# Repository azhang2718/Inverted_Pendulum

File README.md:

# Inverted Pendulum Control System

This page showcases an inverted pendulum on a cart, stabilized in real time by a custom PCB running a PID controller on a TI MSPM0G3507 as part of our final project for **ELEC 327 — Junior Design Lab**.

**Team:** Anthony Zhang · Bilin Yang · Brandon Sung · Setsuna Jiang

---

## Overview

The inverted pendulum is a classic control-theory benchmark: a rigid rod pivots freely on top of a cart that slides along a linear rail, and the controller must drive the cart left and right fast enough to keep the rod balanced upright. The upright position is inherently unstable, so any small tilt has to be detected and corrected before gravity wins.

Our implementation reads the pendulum angle from an AS5600 magnetic encoder over I²C, runs a PID loop at 200 Hz on a custom PCB, and drives a NEMA 17 stepper through a DRV8825 to move the cart along a V-slot aluminum rail.

---

## Hardware

| Component | Part | Role |
|---|---|---|
| Microcontroller | TI MSPM0G3507 | Runs the 200 Hz PID loop |
| Angle sensor | AS5600 magnetic encoder (I²C) | Reads pendulum angle (12-bit) |
| Magnet | Diametrically magnetized, 6 mm OD | Required for AS5600 to detect rotation |
| Motor | NEMA 17 stepper | Drives the cart |
| Motor driver | DRV8825 | STEP/DIR interface, 1/8 microstepping |
| Rail | V-slot aluminum extrusion + GT2 belt | Cart travel |
| Cart | V-slot gantry plate + V-wheels | Rides the rail |
| Bearings | 625RS | Pulley + idler support |
| Endstops | Limit switches (×2) | Homing on startup |
| Power | 12 V / 5 A supply | Motor + logic rail |
| Regulator | LM1117 3.3 V LDO | Logic supply |
| Pendulum | 6 mm × 300 mm steel rod | The thing being balanced |

The full PCB design is in `pcb/` as a KiCad project. Open `*.kicad_pro` in the KiCad project manager to view the schematic and layout

---

## Software

### Control loop

A standard PID controller on the pendulum angle:

- **P** — proportional response to current tilt
- **I** — corrects for slow drift / sensor offset
- **D** — damps oscillation by reacting to angular velocity

The loop runs at 200 Hz. PID gains are stored as integers scaled by 100 so all arithmetic stays in fixed-point — no FPU needed, and the timing is deterministic.

### `config.h`

Every tunable value in the project lives in a single header. The idea is that PID tuning is iterative — you change a number, flash, test, repeat — and having every constant in one place makes that loop fast and error-free.

Things in `config.h`:
- `KP`, `KI`, `KD` — PID gains (scaled ×100)
- `MIN_STEP_RATE`, `MAX_STEP_RATE` — motor speed bounds (prevents stall and runaway)
- `DEADBAND` — angle window where no correction is applied
- `ENGAGE_THRESHOLD` — angle within which the controller activates
- `GIVE_UP_THRESHOLD` — angle past which the controller disengages
- `INTEGRAL_CLAMP` — anti-windup limit on the integral term
- `MOTOR_DIR_SIGN` — direction polarity

### I²C driver (AS5600)

The angle sensor is read over I²C from the raw-angle register. The driver:

1. Waits for the bus to be idle
2. Flushes the TX FIFO
3. Writes the target register address
4. Reads back two bytes → 12-bit angle

Every busy-wait loop has a **timeout counter** that decrements and returns an error code if it hits zero. Without these, a single bad I²C transaction could lock the entire control loop — and on a pendulum that's trying to balance, a hang means it falls instantly.

### Startup sequence

1. Init peripherals (I²C, timers, GPIO)
2. Home the cart against the limit switches and zero the step counter
3. Move cart to center of the rail
4. Wait until the pendulum is within `ENGAGE_THRESHOLD` of vertical
5. Enable PID loop

---

## Building & Flashing

1. Install **Code Composer Studio** (or use the TI Arm Clang toolchain directly).
2. Open the firmware project, build, and flash via the SWD header on the PCB.
3. Adjust values in `inc/config.h` as needed and reflash to tune.

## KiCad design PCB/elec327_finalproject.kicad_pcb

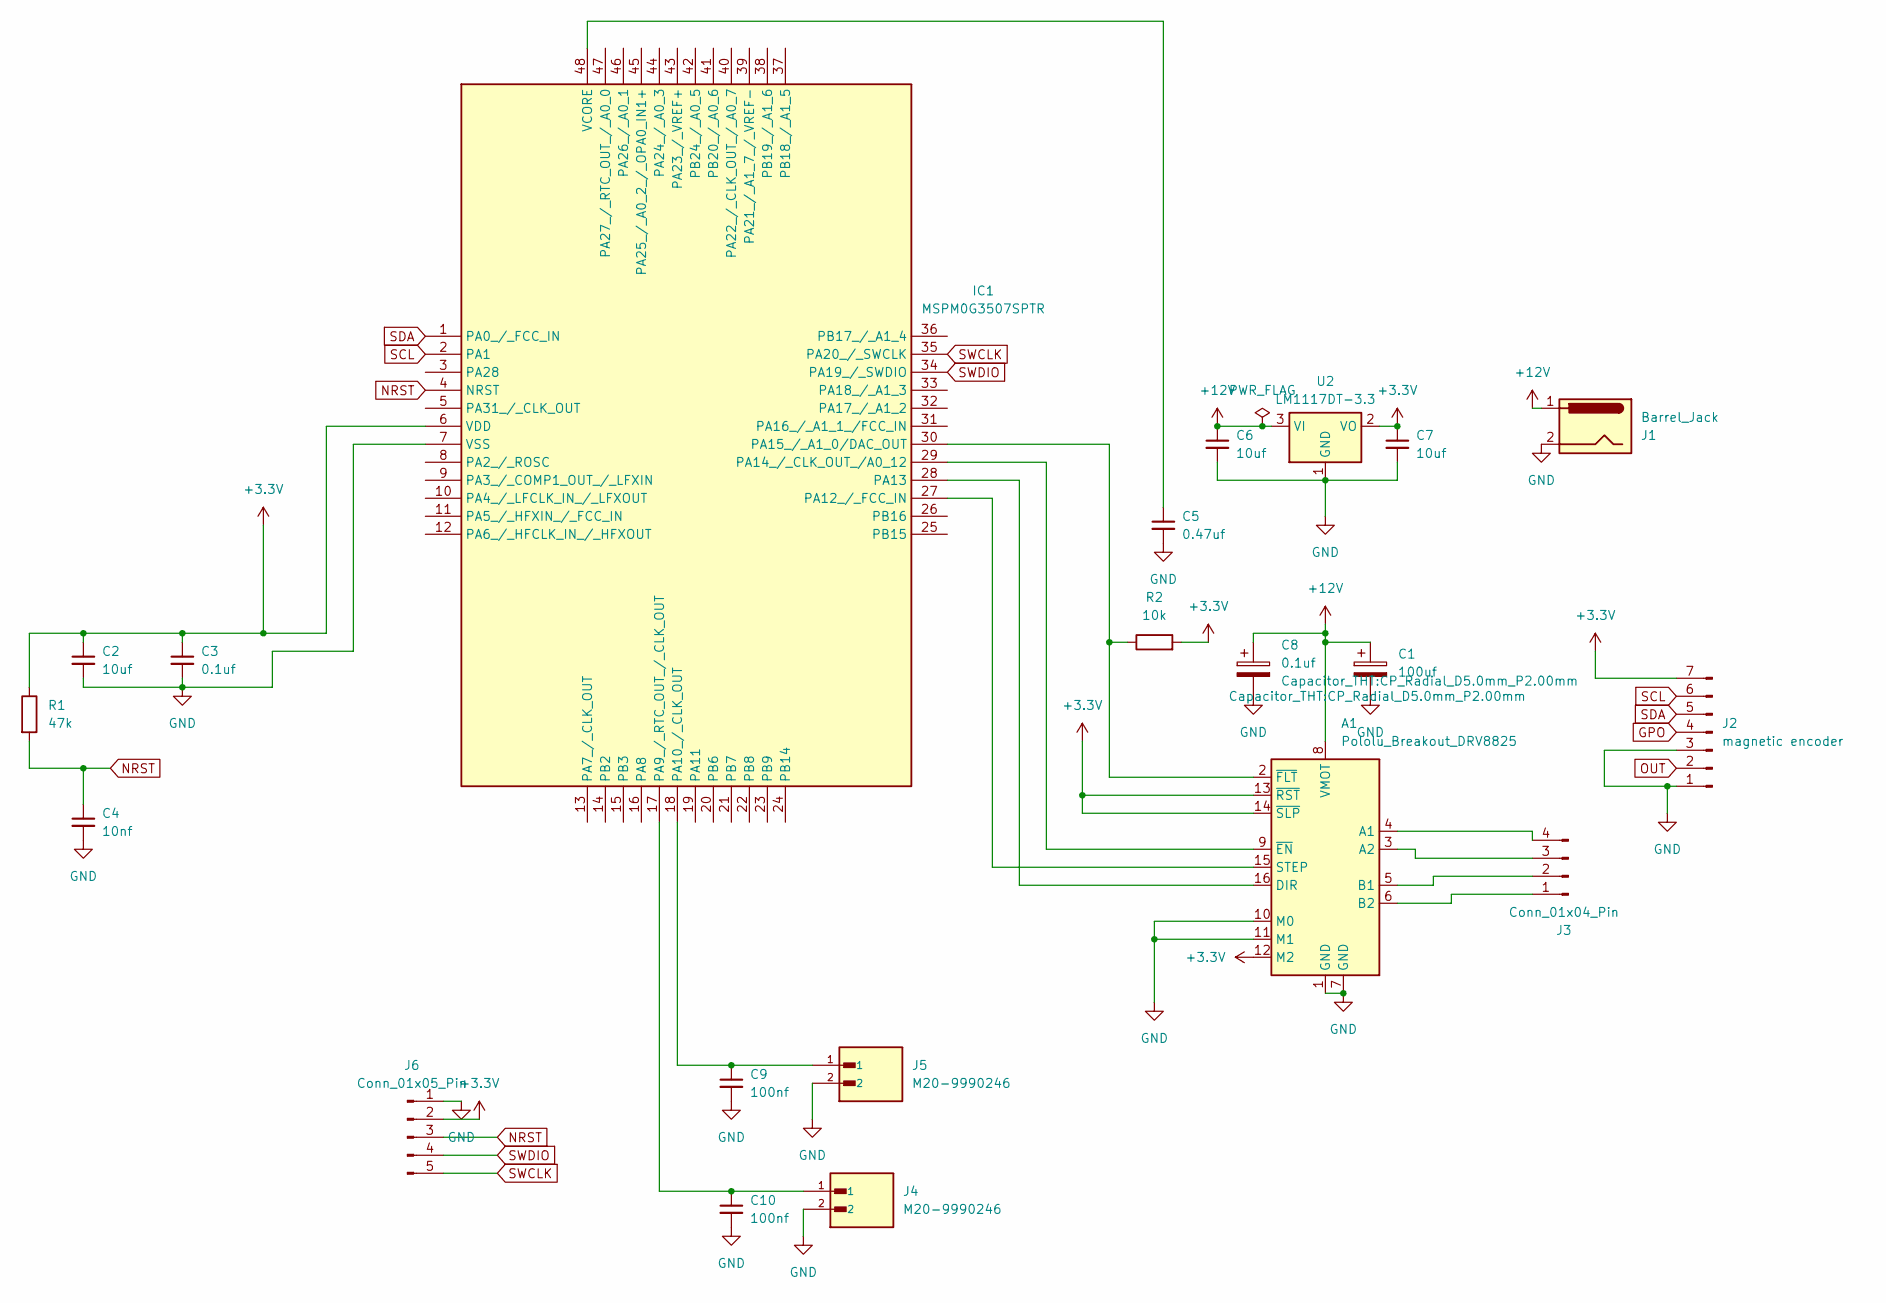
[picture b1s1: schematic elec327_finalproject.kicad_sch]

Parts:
A1: Pololu_Breakout_DRV8825; Pololu_Breakout-16_15.2x20.3mm
C1: 100uf; CP_Radial_D5.0mm_P2.00mm
C2, C6, C7: 10uf; C_0805_2012Metric_Pad1.18x1.45mm_HandSolder
C3: 0.1uf; C_0805_2012Metric_Pad1.18x1.45mm_HandSolder
C4: 10nf; C_0805_2012Metric_Pad1.18x1.45mm_HandSolder
C5: 0.47uf; C_0805_2012Metric_Pad1.18x1.45mm_HandSolder
C8: 0.1uf; CP_Radial_D5.0mm_P2.00mm
C9, C10: 100nf; C_0805_2012Metric_Pad1.18x1.45mm_HandSolder
IC1: MSPM0G3507SPTR; QFP50P900X900X160-48N; Mouser Part Number 595-MSPM0G3507SPTR
J1: Barrel_Jack; BarrelJack_SwitchcraftConxall_RAPC10U_Horizontal
J2: magnetic encoder; PinHeader_1x07_P2.54mm_Vertical
J3: Conn_01x04_Pin; PinHeader_1x04_P2.54mm_Vertical
J4, J5: M20-9990246; HARWIN_M20-9990246; PARTREV 14
J6: Conn_01x05_Pin; PinHeader_1x05_P2.54mm_Vertical
R1: 47k; R_0805_2012Metric_Pad1.20x1.40mm_HandSolder
R2: 10k; R_0805_2012Metric_Pad1.20x1.40mm_HandSolder
U2: LM1117DT-3.3; TO-252-3_TabPin2

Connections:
+3.3V: A1.12 (M2), A1.13 (~RST), A1.14 (~SLP), C2.1, C3.1, C7.1, IC1.6 (VDD), J2.7, J6.2, R1.1, R2.2, U2.2 (VO)
+12V: A1.8 (VMOT), C1.1, C6.1, C8.1, J1.1, U2.3 (VI)
GND: A1.1 (GND), A1.7 (GND), A1.10 (M0), A1.11 (M1), C1.2, C2.2, C3.2, C4.2, C5.2, C6.2, C7.2, C8.2, C9.2, C10.2, IC1.7 (VSS), J1.2, J2.1, J2.3, J4.2, J5.2, J6.1, U2.1 (GND)
GPO: J2.4
NRST: C4.1, IC1.4 (NRST), J6.3, R1.2
unnamed: A1.4 (A1), J3.4
unnamed: A1.3 (A2), J3.3
unnamed: A1.5 (B1), J3.2
unnamed: A1.6 (B2), J3.1
unnamed: A1.16 (DIR), IC1.28 (PA13)
unnamed: A1.15 (STEP), IC1.27 (PA12_/_FCC_IN)
unnamed: A1.9 (~EN), IC1.29 (PA14_/_CLK_OUT_/A0_12)
unnamed: A1.2 (~FLT), IC1.30 (PA15_/_A1_0/DAC_OUT), R2.1
unnamed: C10.1, IC1.17 (PA9_/_RTC_OUT_/_CLK_OUT), J4.1
unnamed: C9.1, IC1.18 (PA10_/_CLK_OUT), J5.1
unnamed: C5.1, IC1.48 (VCORE)
OUT: J2.2
SCL: IC1.2 (PA1), J2.6
SDA: IC1.1 (PA0_/_FCC_IN), J2.5
SWCLK: IC1.35 (PA20_/_SWCLK), J6.5
SWDIO: IC1.34 (PA19_/_SWDIO), J6.4

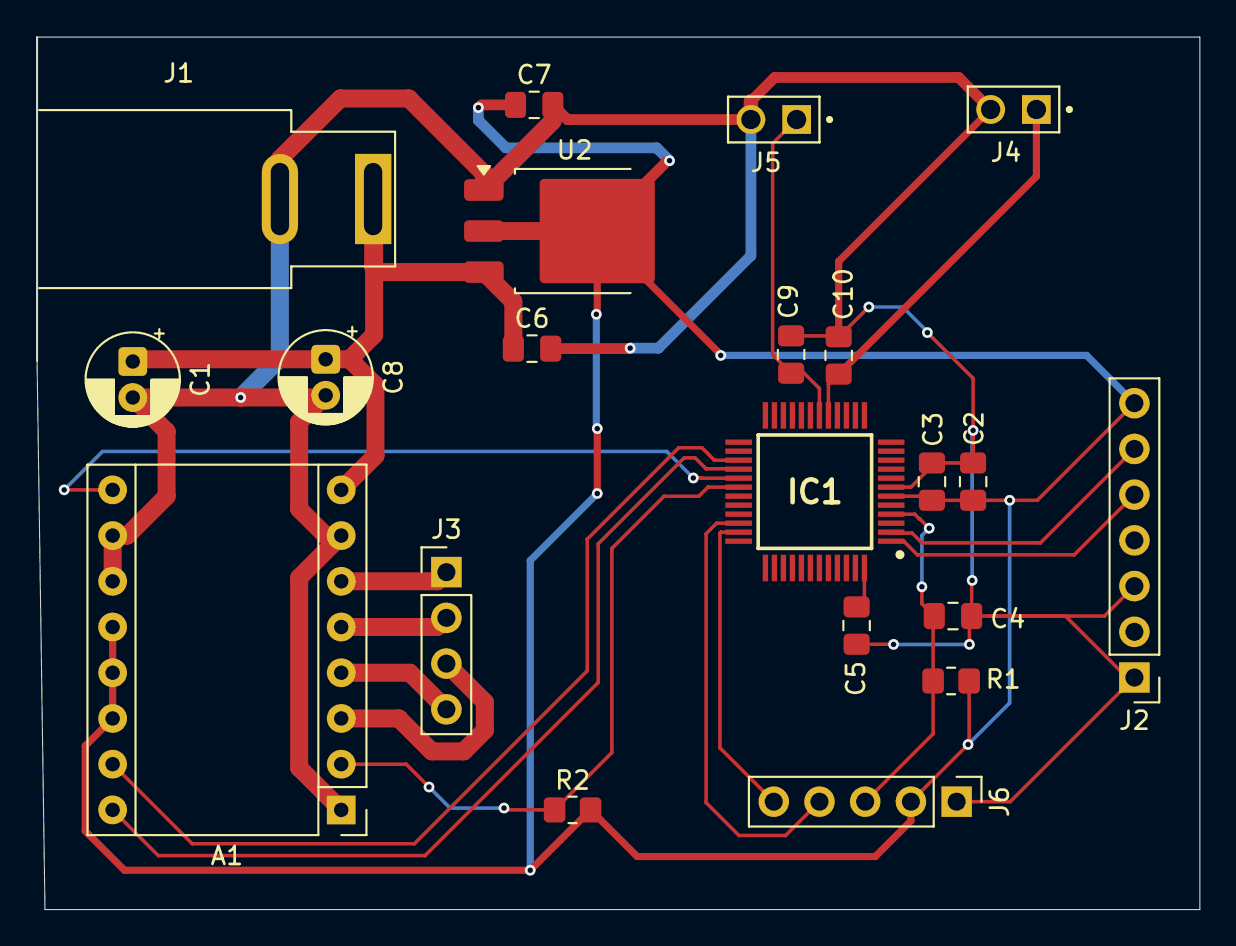
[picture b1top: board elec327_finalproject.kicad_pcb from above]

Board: 2 copper layers, 64.6 x 48.5 mm, 21 parts (0 on the bottom side), 19 nets.

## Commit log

2026-05-05 Add files via upload
    added PCB designs for controlling the inverted pendulum
2026-05-05 Create aasd
2026-05-05 added PCB files
2026-05-05 Create klk
